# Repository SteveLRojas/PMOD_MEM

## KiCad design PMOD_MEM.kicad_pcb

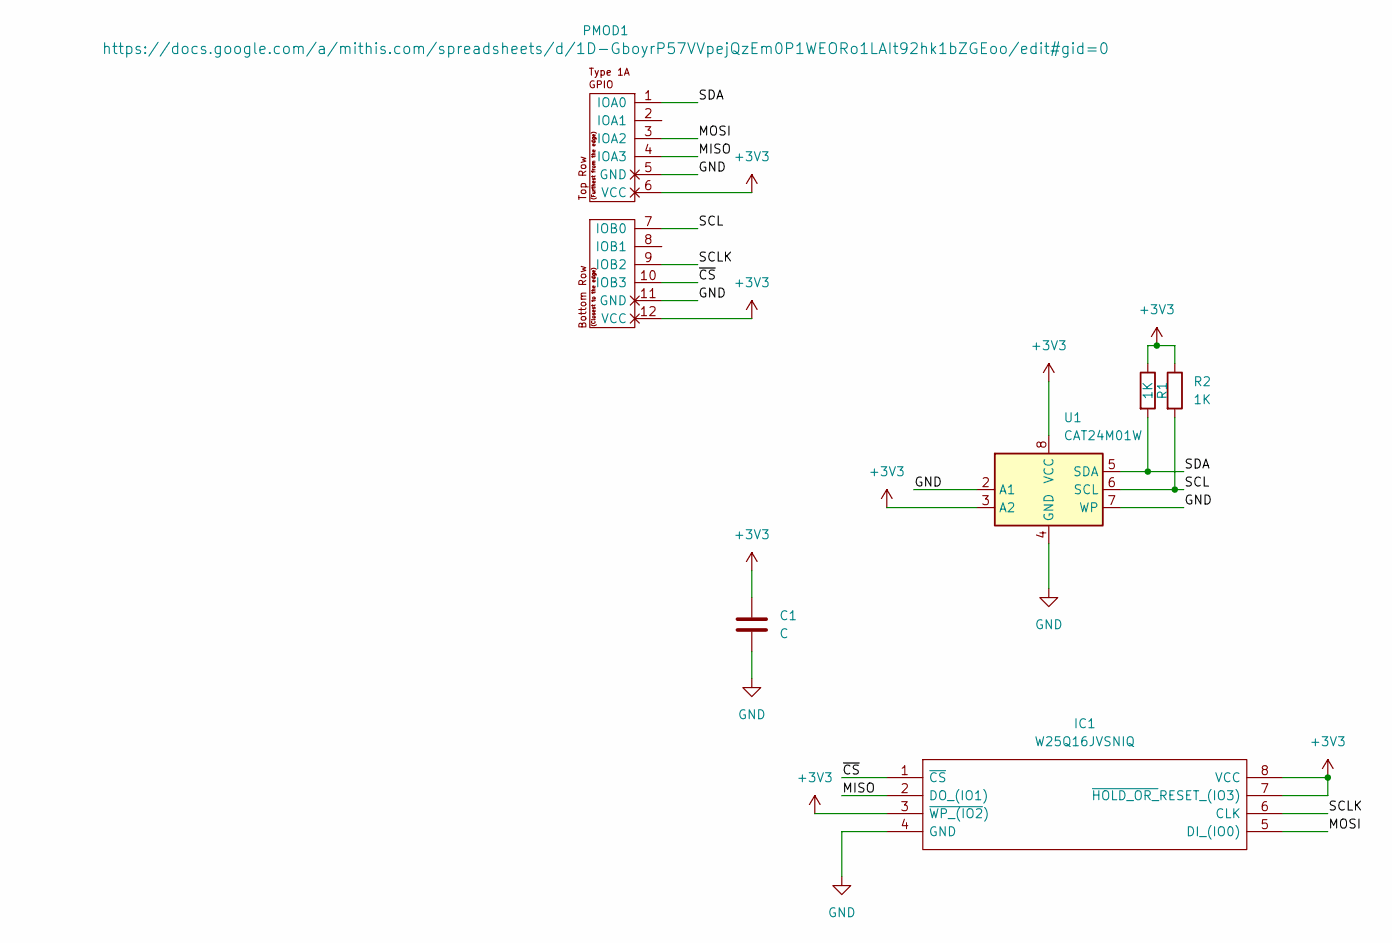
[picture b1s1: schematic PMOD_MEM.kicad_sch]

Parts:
C1: C
IC1: W25Q16JVSNIQ; SOIC127P600X175-8N; Manufacturer_Part_Number W25Q16JVSNIQ; Mouser Part Number 454-W25Q16JVSNIQ
PMOD1: PMOD-Device-x2-Type-1A-GPIO; pmod_pin_array_6x2
R1, R2: 1K
U1: CAT24M01W; SOIC-8_3.9x4.9mm_P1.27mm

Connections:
+3V3: C1.1, IC1.3 (~WP_(IO2)), IC1.7 (~HOLD_OR_RESET_(IO3)), IC1.8 (VCC), PMOD1.6 (VCC), PMOD1.12 (VCC), R1.1, R2.1, U1.3 (A2), U1.8 (VCC)
/MISO: IC1.2 (DO_(IO1)), PMOD1.4 (IOA3)
/MOSI: IC1.5 (DI_(IO0)), PMOD1.3 (IOA2)
/SCL: PMOD1.7 (IOB0), R2.2, U1.6 (SCL)
/SCLK: IC1.6 (CLK), PMOD1.9 (IOB2)
/SDA: PMOD1.1 (IOA0), R1.2, U1.5 (SDA)
/~CS: IC1.1 (~CS), PMOD1.10 (IOB3)
GND: C1.2, IC1.4 (GND), PMOD1.5 (GND), PMOD1.11 (GND), U1.2 (A1), U1.4 (GND), U1.7 (WP)

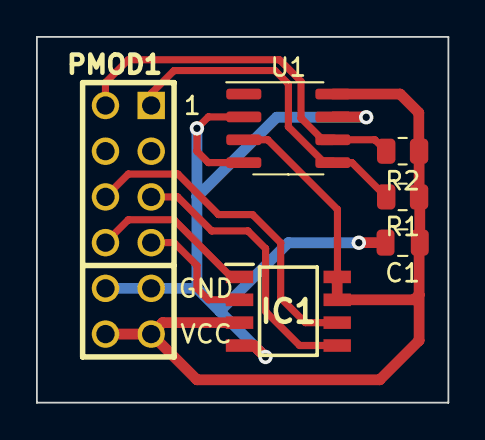
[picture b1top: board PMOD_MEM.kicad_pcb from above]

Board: 2 copper layers, 22.9 x 20.3 mm, 6 parts (0 on the bottom side), 8 nets.

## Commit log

2022-11-25 Added files
2022-11-25 Fixed library paths
